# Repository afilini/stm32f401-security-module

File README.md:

# STM32F401 Security Module

<div style="width: 100%; display: flex; justify-content: space-between;">

</div>

## License

This work is licensed under the [CERN Open Hardware Licence Version 2 - Strongly Reciprocal](LICENSE) license.

## Supporters

This work is supported by a [Brink](https://brink.dev) grant.

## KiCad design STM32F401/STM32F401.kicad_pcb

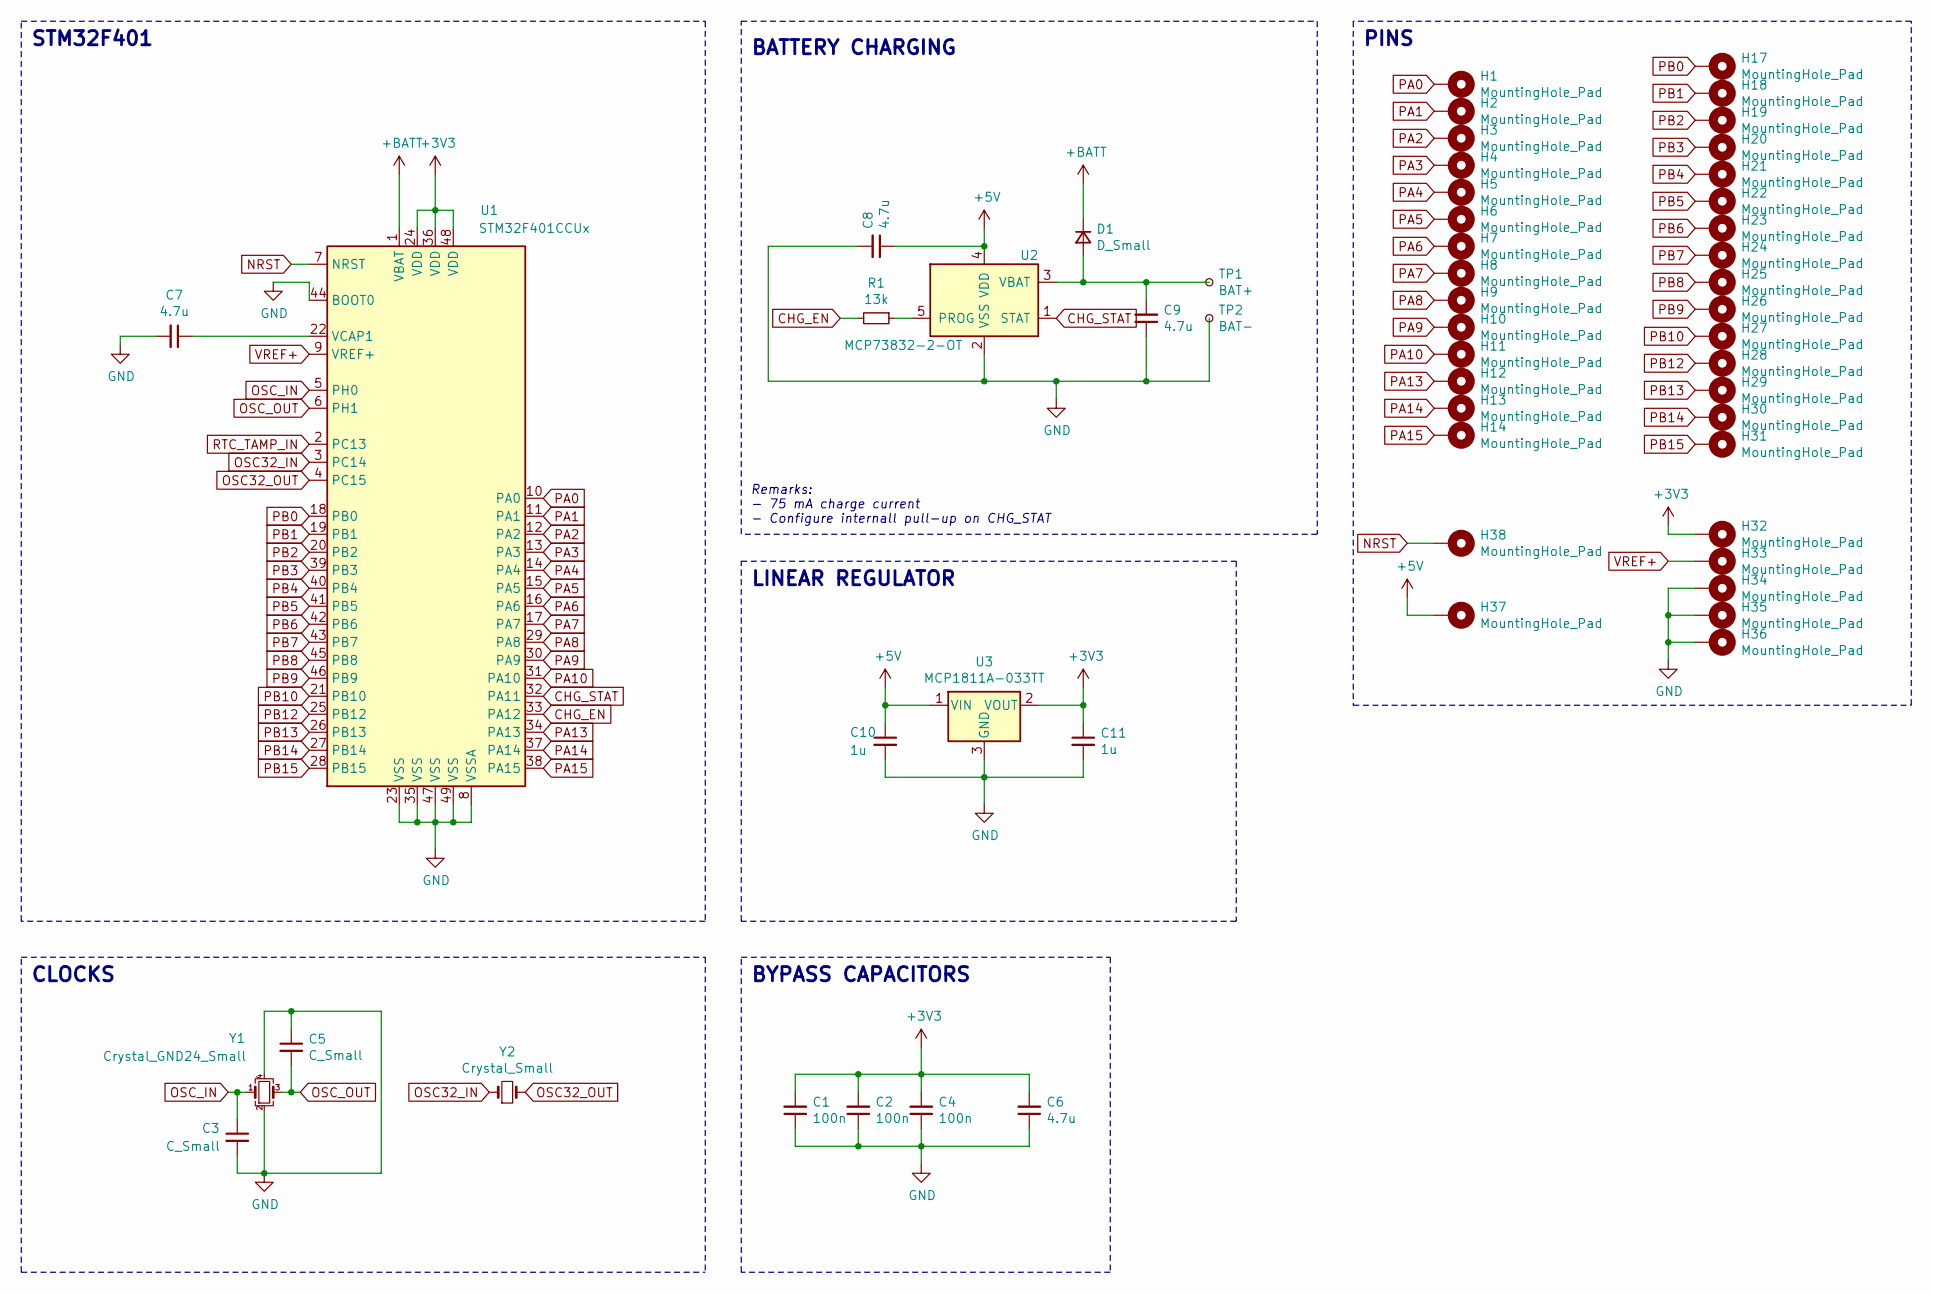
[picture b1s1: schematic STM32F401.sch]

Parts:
C1, C2, C4: 100n; C_0201_0603Metric
C3, C5: C_Small; C_0201_0603Metric
C6, C7, C8, C9: 4.7u; C_0402_1005Metric
C10, C11: 1u; C_0201_0603Metric
D1: D_Small; D_0603_1608Metric
H1, H2, H3, H4, H5, H6, H7, H8, H9, H10, H11, H12, H13, H14, H17, H18, H19, H20, H21, H22, H23, H24, H25, H26, H27, H28, H29, H30, H31, H32, H33, H34, H35, H36, H37, H38: MountingHole_Pad; CastellatedHole_0.6mm
R1: 13k; R_0402_1005Metric
TP1: BAT+; BatteryPad
TP2: BAT-; BatteryPad
U1: STM32F401CCUx; QFN-48-1EP_7x7mm_P0.5mm_EP5.6x5.6mm
U2: MCP73832-2-OT; SOT-23-5
U3: MCP1811A-033TT; TSOT-23
Y1: Crystal_GND24_Small; Crystal_SMD_2016-4Pin_2.0x1.6mm
Y2: Crystal_Small; Crystal_SMD_2012-2Pin_2.0x1.2mm

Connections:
+3V3: C1.2, C2.2, C4.2, C6.2, C11.1, H32.1, U1.24 (VDD), U1.36 (VDD), U1.48 (VDD), U3.2 (VOUT)
+5V: C8.1, C10.1, H37.1, U2.4 (VDD), U3.1 (VIN)
+BATT: D1.1 (K), U1.1 (VBAT)
CHG_EN: R1.2, U1.33 (PA12)
CHG_STAT: U1.32 (PA11), U2.1 (STAT)
GND: C1.1, C2.1, C3.2, C4.1, C5.1, C6.1, C7.2, C8.2, C9.1, C10.2, C11.2, H34.1, H35.1, H36.1, TP2.1, U1.8 (VSSA), U1.23 (VSS), U1.35 (VSS), U1.44 (BOOT0), U1.47 (VSS), U1.49 (VSS), U2.2 (VSS), U3.3 (GND), Y1.2, Y1.4
NRST: H38.1, U1.7 (NRST)
unnamed: C7.1, U1.22 (VCAP1)
unnamed: C9.2, D1.2 (A), TP1.1, U2.3 (VBAT)
unnamed: R1.1, U2.5 (PROG)
OSC32_IN: U1.3 (PC14), Y2.1
OSC32_OUT: U1.4 (PC15), Y2.2
OSC_IN: C3.1, U1.5 (PH0), Y1.1
OSC_OUT: C5.2, U1.6 (PH1), Y1.3
PA0: H1.1, U1.10 (PA0)
PA1: H2.1, U1.11 (PA1)
PA2: H3.1, U1.12 (PA2)
PA3: H4.1, U1.13 (PA3)
PA4: H5.1, U1.14 (PA4)
PA5: H6.1, U1.15 (PA5)
PA6: H7.1, U1.16 (PA6)
PA7: H8.1, U1.17 (PA7)
PA8: H9.1, U1.29 (PA8)
PA9: H10.1, U1.30 (PA9)
PA10: H11.1, U1.31 (PA10)
PA13: H12.1, U1.34 (PA13)
PA14: H13.1, U1.37 (PA14)
PA15: H14.1, U1.38 (PA15)
PB0: H17.1, U1.18 (PB0)
PB1: H18.1, U1.19 (PB1)
PB2: H19.1, U1.20 (PB2)
PB3: H20.1, U1.39 (PB3)
PB4: H21.1, U1.40 (PB4)
PB5: H22.1, U1.41 (PB5)
PB6: H23.1, U1.42 (PB6)
PB7: H24.1, U1.43 (PB7)
PB8: H25.1, U1.45 (PB8)
PB9: H26.1, U1.46 (PB9)
PB10: H27.1, U1.21 (PB10)
PB12: H28.1, U1.25 (PB12)
PB13: H29.1, U1.26 (PB13)
PB14: H30.1, U1.27 (PB14)
PB15: H31.1, U1.28 (PB15)
RTC_TAMP_IN: U1.2 (PC13)
VREF+: H33.1, U1.9 (VREF+)

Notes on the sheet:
STM32F401
CLOCKS
BYPASS CAPACITORS
LINEAR REGULATOR
BATTERY CHARGING
PINS
Remarks: - 75 mA charge current - Configure internall pull-up on CHG_STAT

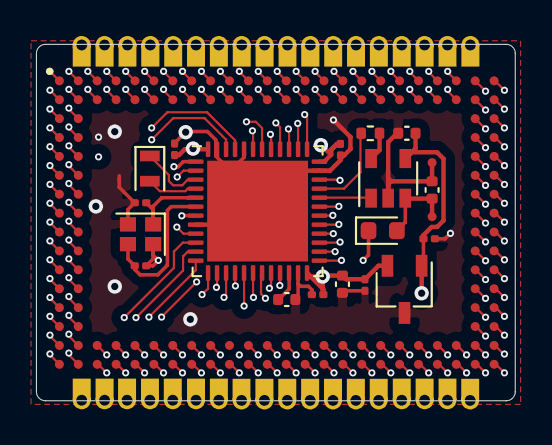
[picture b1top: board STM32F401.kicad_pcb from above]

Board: 4 copper layers, 26.6 x 19.8 mm, 56 parts (0 on the bottom side), 44 nets.

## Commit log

2021-10-11 Swap `PA13` with `PA11`
    Use `PA11` as the `CHG_STAT` pin to free up `PA13` which is needed for
    SWD.
2021-10-13 Fix logo background, add renderings
